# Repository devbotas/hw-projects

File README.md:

This was supposed to be a monorepo, but it is not anymore.

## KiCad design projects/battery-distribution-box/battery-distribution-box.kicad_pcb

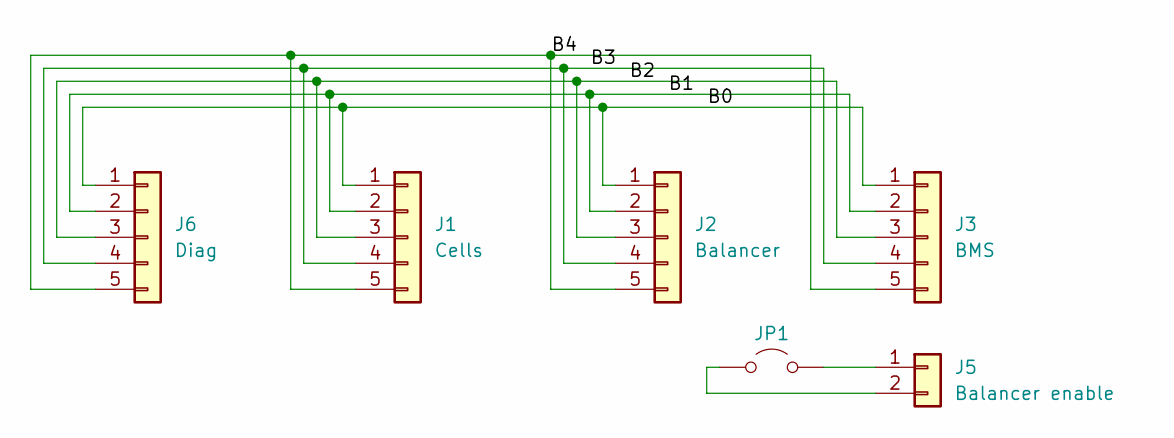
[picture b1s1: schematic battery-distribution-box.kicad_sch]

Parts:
J1: Cells; JST_VH_B5PS-VH_1x05_P3.96mm_Horizontal
J2: Balancer; JST_VH_B5PS-VH_1x05_P3.96mm_Horizontal
J3: BMS; JST_VH_B5PS-VH_1x05_P3.96mm_Horizontal
J5: Balancer enable; JST_VH_B2PS-VH_1x02_P3.96mm_Horizontal
J6: Diag; JST_VH_B5PS-VH_1x05_P3.96mm_Horizontal
JP1: Jumper_2_Open; PinHeader_1x02_P2.54mm_Vertical

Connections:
/B0: J1.1, J2.1, J3.1, J6.1
/B1: J1.2, J2.2, J3.2, J6.2
/B2: J1.3, J2.3, J3.3, J6.3
/B3: J1.4, J2.4, J3.4, J6.4
/B4: J1.5, J2.5, J3.5, J6.5
unnamed: J5.1, JP1.2 (B)
unnamed: J5.2, JP1.1 (A)

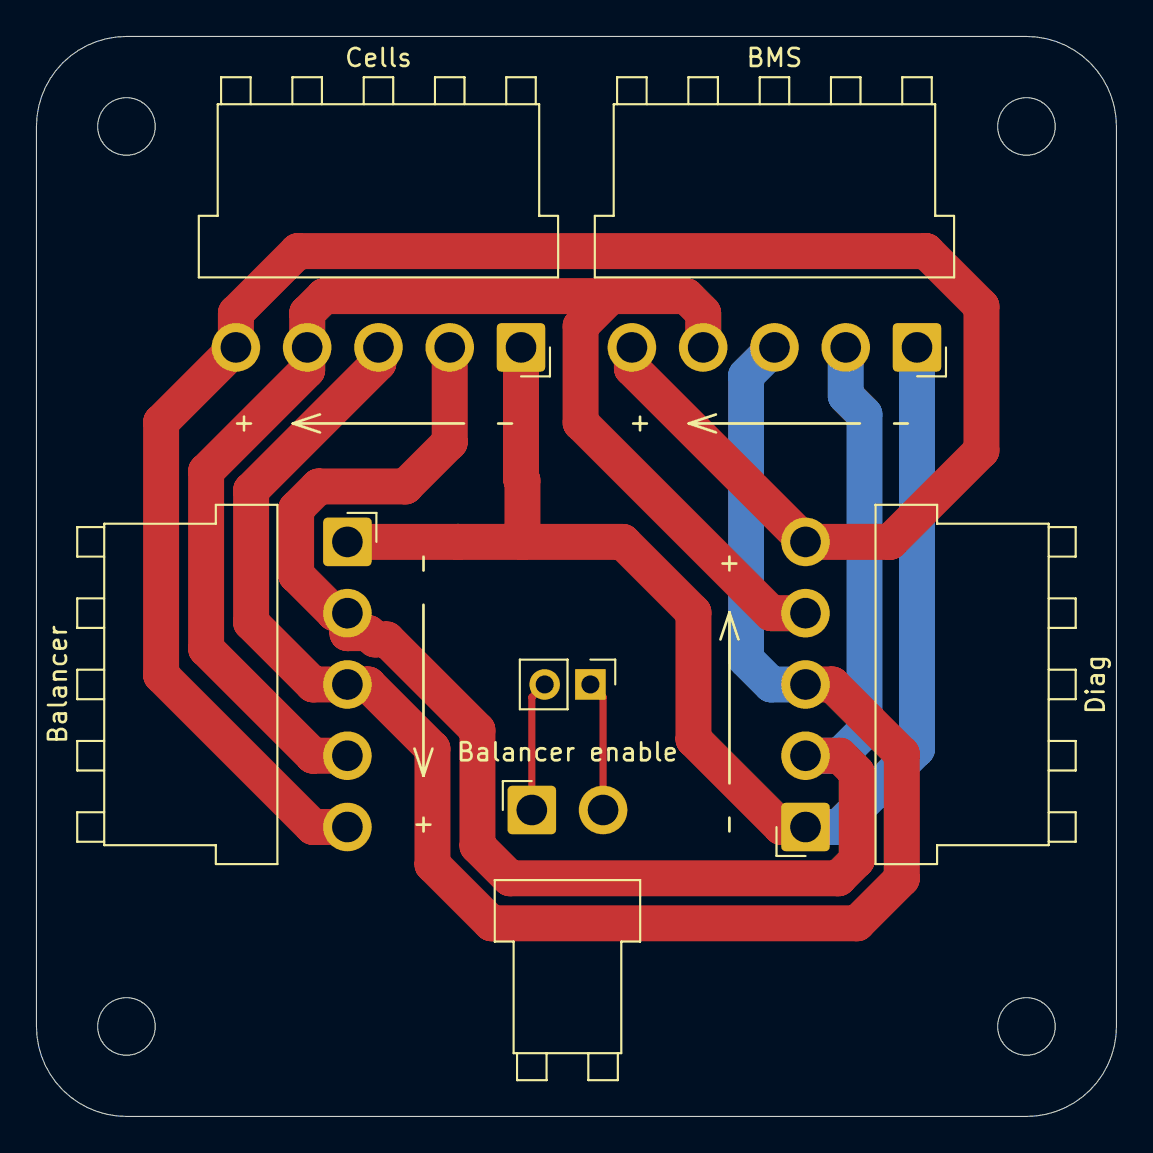
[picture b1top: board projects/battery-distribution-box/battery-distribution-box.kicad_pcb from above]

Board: 2 copper layers, 60.0 x 60.0 mm, 6 parts (0 on the bottom side), 7 nets.

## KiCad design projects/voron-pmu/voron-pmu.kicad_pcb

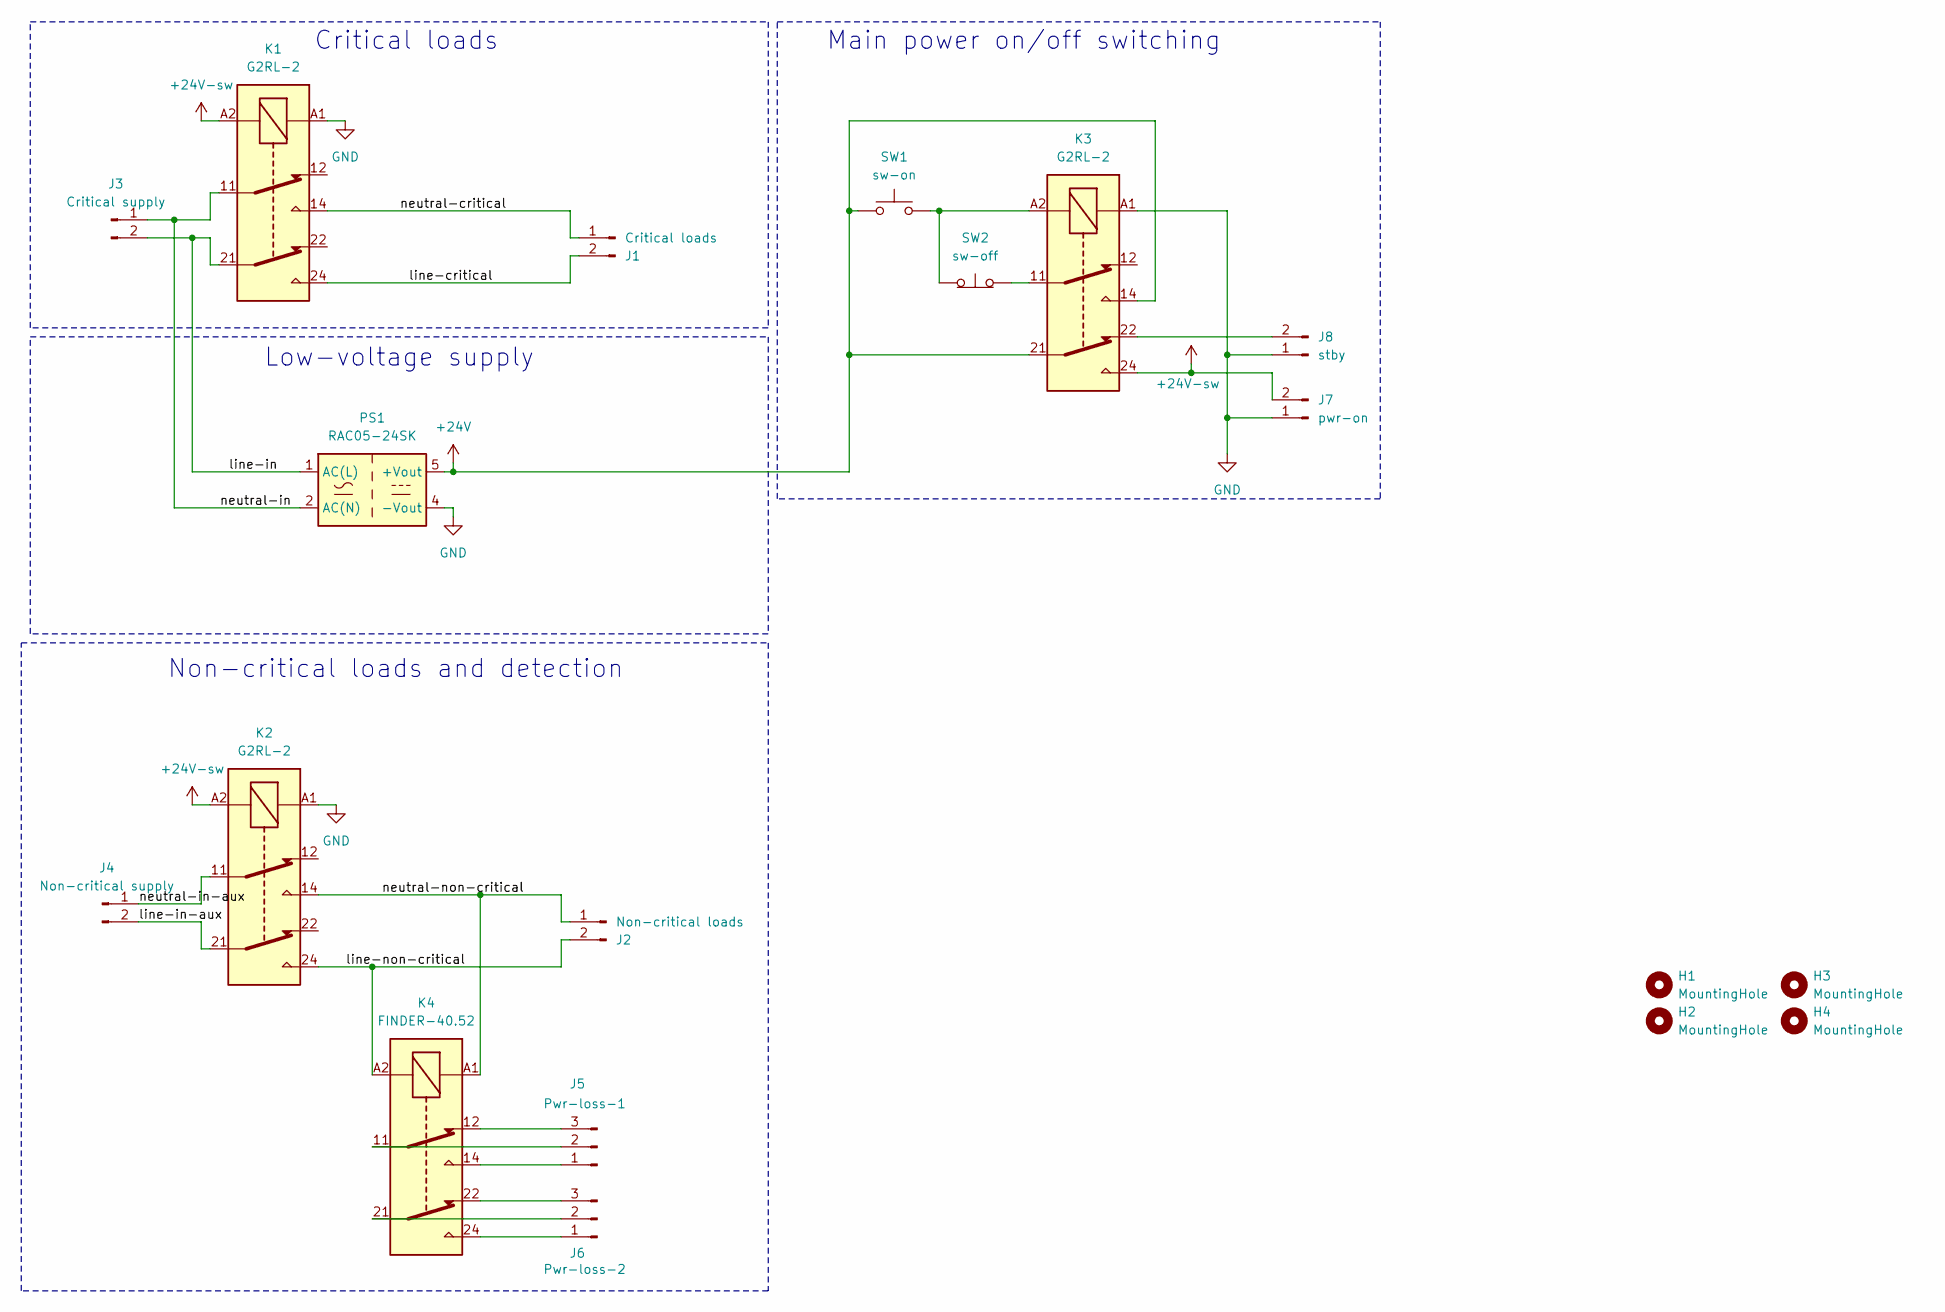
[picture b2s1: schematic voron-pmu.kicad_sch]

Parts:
H1, H2, H3, H4: MountingHole; MountingHole_3.2mm_M3
J1: Critical loads; PhoenixContact_MSTBVA_2,5_2-G-5,08_1x02_P5.08mm_Vertical
J2: Non-critical loads; PhoenixContact_MSTBVA_2,5_2-G-5,08_1x02_P5.08mm_Vertical
J3: Critical supply; PhoenixContact_MSTBVA_2,5_2-G-5,08_1x02_P5.08mm_Vertical
J4: Non-critical supply; PhoenixContact_MSTBVA_2,5_2-G-5,08_1x02_P5.08mm_Vertical
J5: Pwr-loss-1; JST_XH_B3B-XH-A_1x03_P2.50mm_Vertical
J6: Pwr-loss-2; JST_XH_B3B-XH-A_1x03_P2.50mm_Vertical
J7: pwr-on; JST_XH_B2B-XH-A_1x02_P2.50mm_Vertical
J8: stby; JST_XH_B2B-XH-A_1x02_P2.50mm_Vertical
K1, K2, K3: G2RL-2; Relay_DPDT_Omron_G2RL-2
K4: FINDER-40.52; Relay_DPDT_Finder_40.52
PS1: RAC05-24SK; Converter_ACDC_RECOM_RAC04-xxSGx_THT
SW1: sw-on; JST_XH_B2B-XH-A_1x02_P2.50mm_Vertical
SW2: sw-off; JST_XH_B2B-XH-A_1x02_P2.50mm_Vertical

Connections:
+24V: K3.14, K3.21, PS1.5 (+Vout), SW1.1
+24V-sw: J7.2, K1.A2, K2.A2, K3.24
/line-critical: J1.2, K1.24
/line-in: J3.2, K1.21, PS1.1 (AC(L))
/line-in-aux: J4.2, K2.21
/line-non-critical: J2.2, K2.24, K4.A2
/neutral-critical: J1.1, K1.14
/neutral-in: J3.1, K1.11, PS1.2 (AC(N))
/neutral-in-aux: J4.1, K2.11
/neutral-non-critical: J2.1, K2.14, K4.A1
GND: J7.1, J8.1, K1.A1, K2.A1, K3.A1, PS1.4 (-Vout)
unnamed: J5.1, K4.14
unnamed: J5.2, K4.11
unnamed: J5.3, K4.12
unnamed: J6.1, K4.24
unnamed: J6.2, K4.21
unnamed: J6.3, K4.22
unnamed: J8.2, K3.22
unnamed: K3.A2, SW1.2, SW2.1 (A)
unnamed: K3.11, SW2.2 (B)

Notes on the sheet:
Low-voltage supply
Non-critical loads and detection
Critical loads
Main power on/off switching

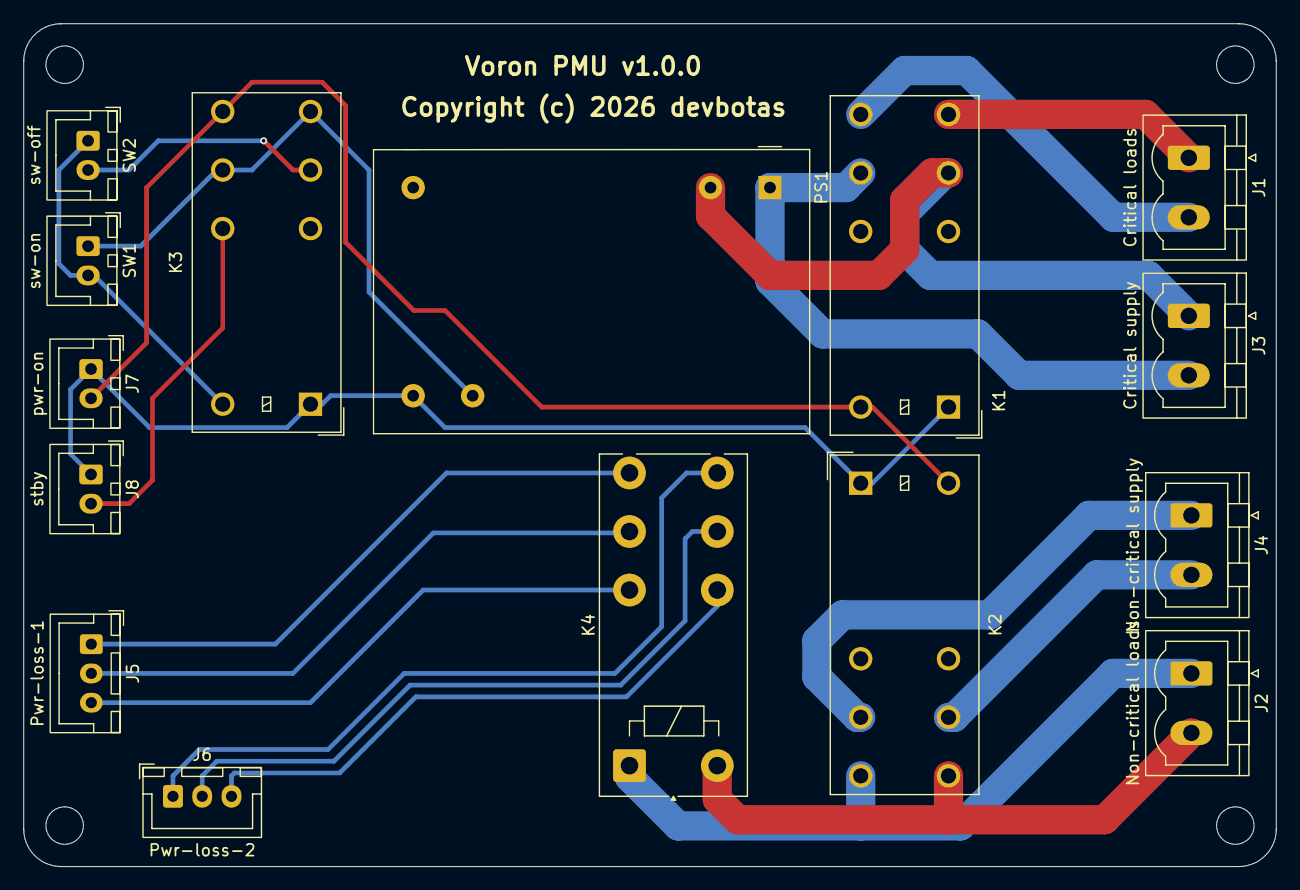
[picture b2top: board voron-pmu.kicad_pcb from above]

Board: 2 copper layers, 107.0 x 72.0 mm, 19 parts (0 on the bottom side), 20 nets.

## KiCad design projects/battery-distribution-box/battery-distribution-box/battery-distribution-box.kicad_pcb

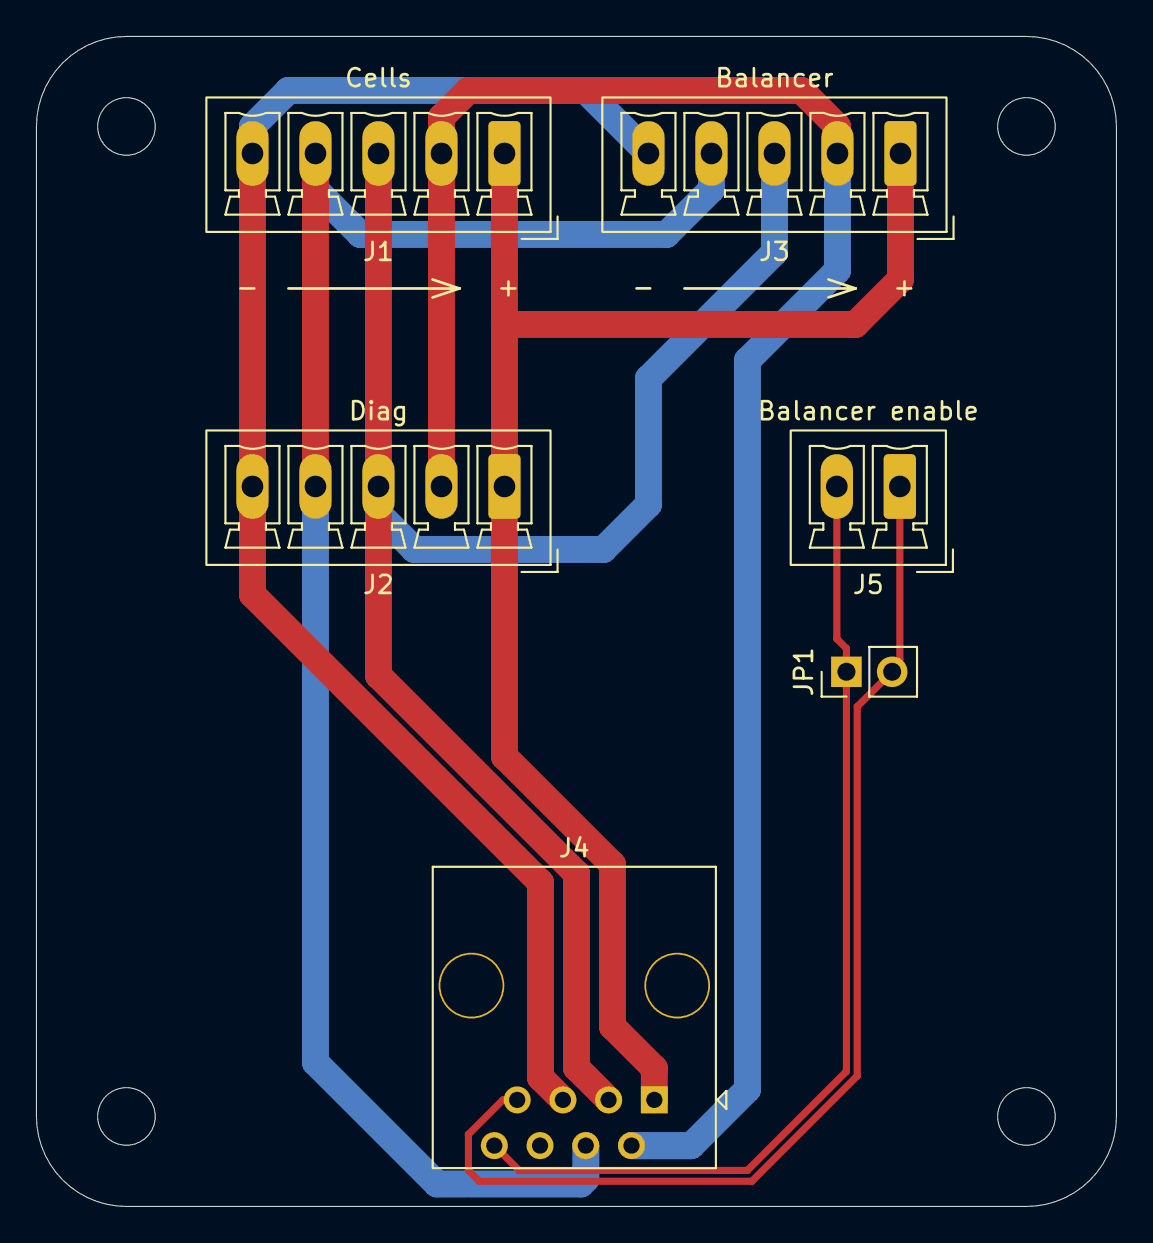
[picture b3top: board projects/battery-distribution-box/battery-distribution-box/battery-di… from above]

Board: 2 copper layers, 60.0 x 65.0 mm, 6 parts (0 on the bottom side), 7 nets.

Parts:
J1: Cells; PhoenixContact_MCV_1,5_5-G-3.5_1x05_P3.50mm_Vertical
J2: Diag; PhoenixContact_MCV_1,5_5-G-3.5_1x05_P3.50mm_Vertical
J3: Balancer; PhoenixContact_MCV_1,5_5-G-3.5_1x05_P3.50mm_Vertical
J4: Output; RJ45_OST_PJ012-8P8CX_Vertical
J5: Balancer enable; PhoenixContact_MCV_1,5_2-G-3.5_1x02_P3.50mm_Vertical
JP1: Jumper_2_Open; PinHeader_1x02_P2.54mm_Vertical

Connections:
unnamed: J1.1, J2.1, J3.1, J4.1
unnamed: J1.2, J2.2, J3.2, J4.2
unnamed: J1.3, J2.3, J3.3, J4.3
unnamed: J1.4, J2.4, J3.4, J4.4
unnamed: J1.5, J2.5, J3.5, J4.5
unnamed: J4.7, J5.1, JP1.2 (B)
unnamed: J4.8, J5.2, JP1.1 (A)

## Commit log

2026-03-20 Adding gitignore.
2026-03-20 Drafting.
2026-03-20 Playing around.
2026-03-20 Re-saving.
2026-03-23 Prettyfing schematics.
2026-03-23 Replacing relays with Omron. Will route now.
2026-03-23 Battling Mouser and Kicad.
2026-04-01 Saving to version 10.
2026-04-01 Ignoring KiCad history subrepo.
2026-04-01 Saving PCB to format 10.
2026-04-01 Adding pwr-good and stby indications.
2026-04-01 Moving on/off switches to the high side.
2026-04-02 Routing a new revision.
2026-04-02 Ignoring outputs.
2026-04-02 Adding labels.
2026-04-02 Updating readme.
2026-04-03 Adding mounting models and some other tweaks.
2026-04-07 Adding initial draft of batterry distribution box.
2026-04-07 Project was overnested.
2026-04-23 Extracting voron-pmu into a separate project.
2026-04-27 Moving to JST VH connectors. They are cheaper and easier to source.
2026-04-27 Battery distribution board moved to separate repo.

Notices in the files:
projects/battery-distribution-box/battery-distribution-box.kicad_pcb:
Copyright (c) 2026 devbotas
